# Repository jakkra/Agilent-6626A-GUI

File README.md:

# Remote UI control of Agilent 6626A DC Power Supply 
Making an old (but very good) power supply a bit more modern by giving it a nice new touch UI with remote control.

The idea is to be able to move away the really big power supply and only have the new front panel visible.<br>
The UI is running on a Raspberry Pi with a 7" touch screen.

## GPIB Communication
To communicate with the instrument, I'm using the awesome [AR488 GPIB <-> UART FW](https://github.com/Twilight-Logic/AR488/tree/master). It is flashed on an Arduino Nano sitting on a simple custom PCB, which breaks out the GPIB connector. This setup allows you to easily interact with test instruments.

## The PCB

The power supply outputs are placed on the back of the instrument making them a bit hard to access. To solve this I designed a breakout PCB that through screw terminals guide the four power supply outputs to easily accessible banana plugs.

The breakout PCB also includes some extra features:
- USB A connector that connects to the power supply through the GPIB <-> UART bridge.
- Two USB C connectors that can connect to different hosts, such as a computer in addition to the Raspberry Pi.
- USB switch (controlled through a switch) that routes the GPIB USB to either of the two USB C connectors.
- 4 optocouplers controlling 4 LEDs (one for each output) to indicate if power is enabled or not.
  - Due to the four outputs having separate grounds, I use optocouplers to isolate the LED from the actual output.

## The UI
Used PyQt5 to design a decent looking UI to graphically interact with the power supply.
Behind the scenes GPIB commands are sent to the power supply to make it do what we want.

### GPIB Commands
The control interface is quite simple. For example to set output 1 to 5V, max 0.1A it's as simple as this:
```plaintext
VSET 1,1.8000
ISET 1,0.1000
```
You can also query stuff such as the actual voltage at the output and current being drawn. This is what's being used to display the realtime plots.
```plaintext
VOUT? 1
<now read response>
IOUT? 1
<now read response>
```

## Using the sensing inputs
The sensing inputs are also routed to the new front panel. The default way to use them is to short the V_out to Sense+ and GND to Sense- on the front panel using a simple 2-1 banana plug. When these are connected, the power supply's sense feature will compensate for voltage loss in the cables running from the back of the power supply to the new front panel.

To allow for more advanced use, simply remove the 2-1 banana plug, giving you free access to the Sense+ and Sense- on each output.

## ToDo
- The UI needs some tweaking to be easier to use on the 7 inch touch screen connected to a Raspberry Pi.

## References
[6628A Power Supply User Guide](https://www.keysight.com/us/en/assets/9018-01123/user-manuals/9018-01123.pdf)

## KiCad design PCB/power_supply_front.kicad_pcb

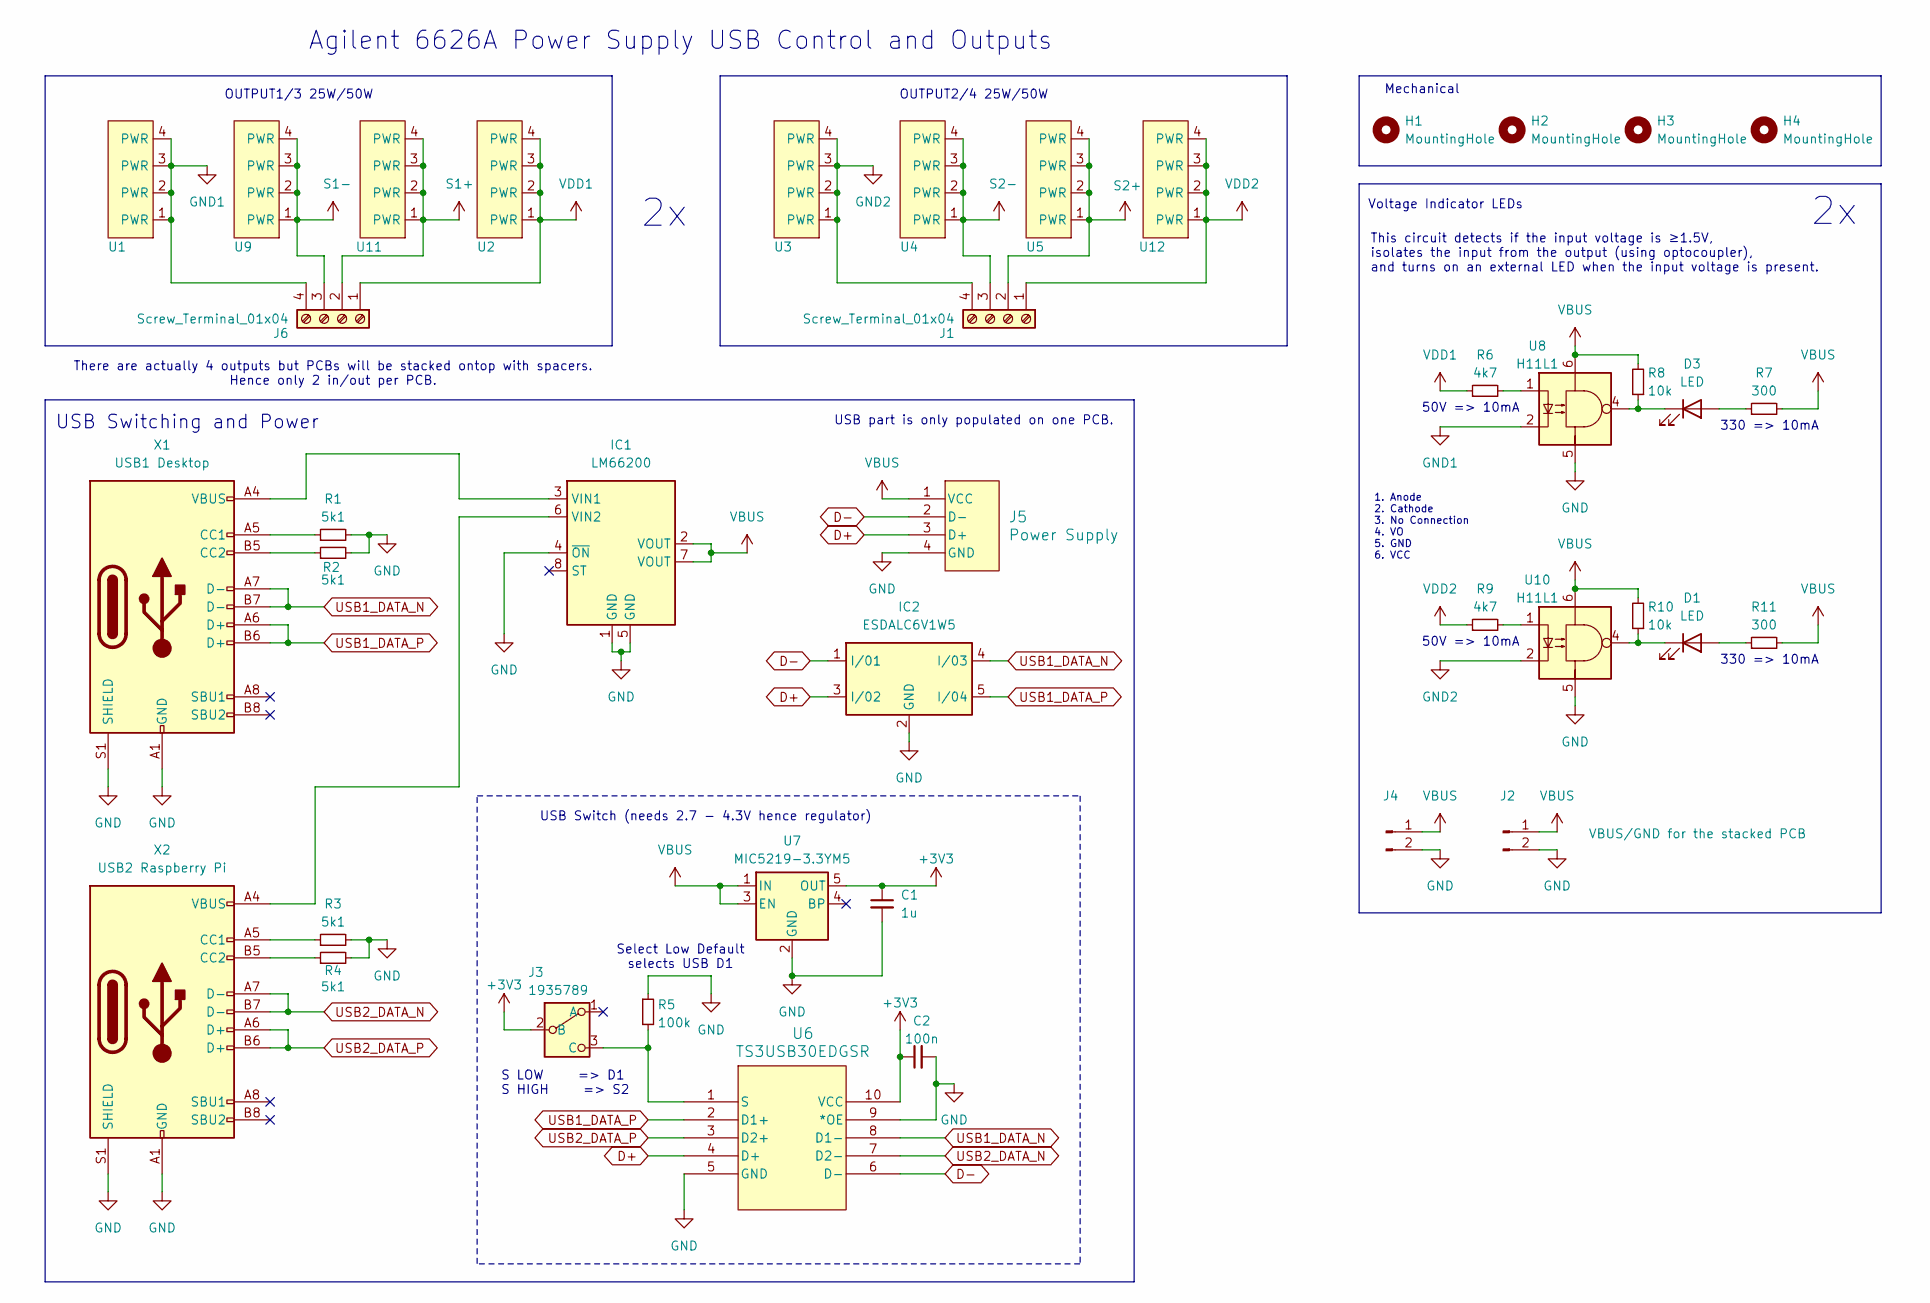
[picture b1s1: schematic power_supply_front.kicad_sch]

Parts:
C1: 1u; C_0603_1608Metric
C2: 100n; C_0603_1608Metric
D1, D3: LED; LED_D5.0mm
H1, H2, H3, H4: MountingHole; MountingHole_4mm_Pad_TopBottom
IC1: LM66200; SOT-5X3-8
IC2: ESDALC6V1W5; SOT-325-5
J1, J6: Screw_Terminal_01x04; PHOENIX_1935789
J2, J4: VBUS/GND for the stacked PCB; PinSocket_1x02_P2.54mm_Vertical
J3: 1935789; EG1213
J5: Power Supply; CONN4_UJ2-AH_CUD
R1, R2, R3, R4: 5k1; R_0603_1608Metric
R5: 100k; R_0603_1608Metric
R6, R9: 4k7; R_0603_1608Metric
R7, R11: 300; R_0603_1608Metric
R8, R10: 10k; R_0603_1608Metric
U1, U2, U3, U4, U5, U9, U11, U12: CT3151SP
U6: TS3USB30EDGSR; DGS10
U7: MIC5219-3.3YM5; SOT-23-5
U8, U10: H11L1; DIP-6_W10.16mm
X1: USB1 Desktop; USB_C_Receptacle_GCT_USB4105-xx-A_16P_TopMnt_Horizontal
X2: USB2 Raspberry Pi; USB_C_Receptacle_GCT_USB4105-xx-A_16P_TopMnt_Horizontal

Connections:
+3V3: C1.1, C2.1, J3.2 (B), U6.10 (VCC), U7.5 (OUT)
D+: IC2.3 (I/02), J5.3 (D+), U6.4 (D+)
D-: IC2.1 (I/01), J5.2 (D-), U6.6 (D-)
GND: C1.2, C2.2, IC1.1 (GND), IC1.4 (~ON), IC1.5 (GND), IC2.2 (GND), J2.2, J4.2, J5.4 (GND), R1.2, R2.2, R3.2, R4.2, R5.1, U6.5 (GND), U6.9 (*OE), U7.2 (GND), U8.5, U10.5, X1.A1 (GND), X1.A12 (GND), X1.B1 (GND), X1.B12 (GND), X1.S1 (SHIELD), X2.A1 (GND), X2.A12 (GND), X2.B1 (GND), X2.B12 (GND), X2.S1 (SHIELD)
GND1: J6.4, U1.1 (PWR), U1.2 (PWR), U1.3 (PWR), U1.4 (PWR), U8.2
GND2: J1.4, U3.1 (PWR), U3.2 (PWR), U3.3 (PWR), U3.4 (PWR), U10.2
unnamed: D1.2 (A), R11.1
unnamed: D1.1 (K), R10.1, U10.4
unnamed: D3.2 (A), R7.1
unnamed: D3.1 (K), R8.1, U8.4
unnamed: IC1.3 (VIN1), X1.A4 (VBUS), X1.A9 (VBUS), X1.B4 (VBUS), X1.B9 (VBUS)
unnamed: IC1.6 (VIN2), X2.A4 (VBUS), X2.A9 (VBUS), X2.B4 (VBUS), X2.B9 (VBUS)
unnamed: J3.3 (C), R5.2, U6.1 (S)
unnamed: R6.2, U8.1
unnamed: R9.2, U10.1
unnamed: R1.1, X1.A5 (CC1)
unnamed: R2.1, X1.B5 (CC2)
unnamed: R3.1, X2.A5 (CC1)
unnamed: R4.1, X2.B5 (CC2)
S1+: J6.2, U11.1 (PWR), U11.2 (PWR), U11.3 (PWR), U11.4 (PWR)
S1-: J6.3, U9.1 (PWR), U9.2 (PWR), U9.3 (PWR), U9.4 (PWR)
S2+: J1.2, U5.1 (PWR), U5.2 (PWR), U5.3 (PWR), U5.4 (PWR)
S2-: J1.3, U4.1 (PWR), U4.2 (PWR), U4.3 (PWR), U4.4 (PWR)
USB1_DATA_N: IC2.4 (I/03), U6.8 (D1-), X1.A7 (D-), X1.B7 (D-)
USB1_DATA_P: IC2.5 (I/04), U6.2 (D1+), X1.A6 (D+), X1.B6 (D+)
USB2_DATA_N: U6.7 (D2-), X2.A7 (D-), X2.B7 (D-)
USB2_DATA_P: U6.3 (D2+), X2.A6 (D+), X2.B6 (D+)
VBUS: IC1.2 (VOUT), IC1.7 (VOUT), J2.1, J4.1, J5.1 (VCC), R7.2, R8.2, R10.2, R11.2, U7.1 (IN), U7.3 (EN), U8.6, U10.6
VDD1: J6.1, R6.1, U2.1 (PWR), U2.2 (PWR), U2.3 (PWR), U2.4 (PWR)
VDD2: J1.1, R9.1, U12.1 (PWR), U12.2 (PWR), U12.3 (PWR), U12.4 (PWR)

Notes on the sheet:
Agilent 6626A Power Supply USB Control and Outputs
50V => 10mA
Mechanical
There are actually 4 outputs but PCBs will be stacked ontop with spacers. Hence only 2 in/out per PCB.
USB Switch (needs 2.7 - 4.3V hence regulator)
USB part is only populated on one PCB.
Select Low Default selects USB D1
This circuit detects if the input voltage is ≥1.5V, isolates the input from the output (using optocoupler), and turns on an external LED when the input voltage is present.
S LOW => D1 S HIGH => S2
OUTPUT1/3 25W/50W
Voltage Indicator LEDs
1. Anode 2. Cathode 3. No Connection 4. VO 5. GND 6. VCC
330 => 10mA
USB Switching and Power
OUTPUT2/4 25W/50W

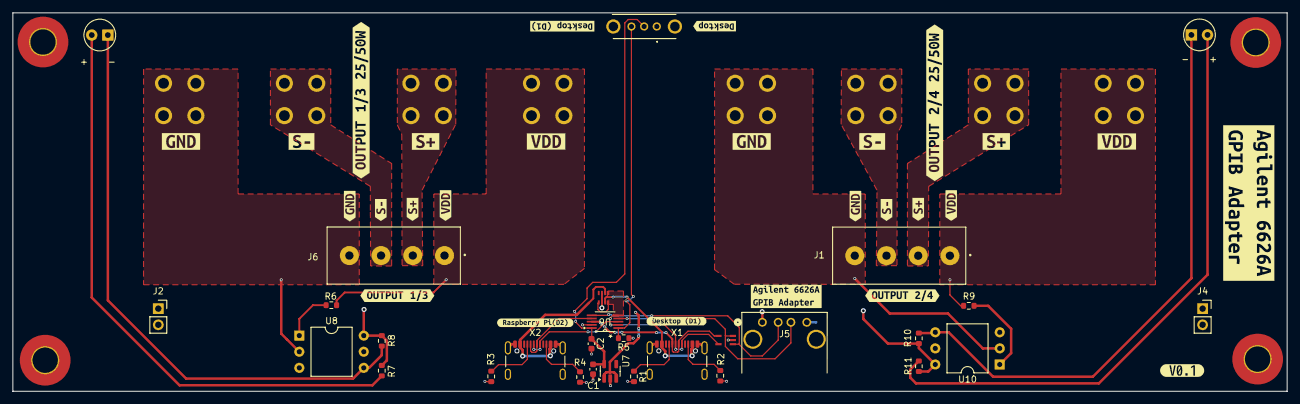
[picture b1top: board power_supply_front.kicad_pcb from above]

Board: 2 copper layers, 200.9 x 59.7 mm, 69 parts (1 on the bottom side), 30 nets.

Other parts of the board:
kibuzzard-674E1A25: G***; kibuzzard-674E1A25
kibuzzard-674E1A52: G***; kibuzzard-674E1A52
kibuzzard-674E1B6F: G***; kibuzzard-674E1B6F
kibuzzard-674E1B37: G***; kibuzzard-674E1B37
kibuzzard-674E1B67: G***; kibuzzard-674E1B67
kibuzzard-674E1BAB: G***; kibuzzard-674E1BAB
kibuzzard-674E1BF2: G***; kibuzzard-674E1BF2
kibuzzard-674F779A: G***; kibuzzard-674F779A
kibuzzard-674F7791: G***; kibuzzard-674F7791
kibuzzard-6759F0B5: G***; kibuzzard-6759F0B5
kibuzzard-67536A0A, kibuzzard-67536A0A#2: G***; kibuzzard-67536A0A
kibuzzard-67536AC1: G***; kibuzzard-67536AC1
kibuzzard-67536BD6: G***; kibuzzard-67536BD6
kibuzzard-675368B8, kibuzzard-675368B8#2: G***; kibuzzard-675368B8
kibuzzard-675368D0, kibuzzard-675368D0#2: G***; kibuzzard-675368D0
kibuzzard-675368D9, kibuzzard-675368D9#2: G***; kibuzzard-675368D9
kibuzzard-675368DE, kibuzzard-675368DE#2: G***; kibuzzard-675368DE
kibuzzard-675369A2, kibuzzard-675369A2#2: G***; kibuzzard-675369A2
kibuzzard-675369E9, kibuzzard-675369E9#2: G***; kibuzzard-675369E9
kibuzzard-675369FB, kibuzzard-675369FB#2: G***; kibuzzard-675369FB

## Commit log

2024-11-24 Initial power supply GUI.
2024-11-24 Add dark theme colors and tweak UI.
2024-11-25 Add config panel to connect to instrument with terminal output.
2024-11-25 Implement API for the power supply commands (not tested).
2024-11-25 Reset supply on connect. Add ability to set text to supply screen.
2024-11-26 Add mock and debug option to Power Supply API.
2024-11-26 Fetch actual volage and current consumed when a output is on.
2024-11-26 Add plotting in new window for the actual output current.
2024-12-04 PCB: Add KiCad project for the output and control interface.
2024-12-06 Adjust plug spacing. Add label connector pinout on silkscreen.
2024-12-08 UI: Tested on real HW, fixes needed for that.
2025-02-10 UI: Fullscreen support and improve the UI for smaller resolution screen.
2025-02-10 PCB: Small adjustments.
2025-02-10 Describe the project in the README.
2025-02-12 CAD: Add the enclosure design.
2025-08-28 UI: Improve setting voltage/current on small screen by using a modal popup.
2025-08-28 UI: Add automatic display power management to turn off the display after a period of inactivity.
    Turns off screen and backlight after 5 minutes.
    Touch the screen to quickly wake it up.
